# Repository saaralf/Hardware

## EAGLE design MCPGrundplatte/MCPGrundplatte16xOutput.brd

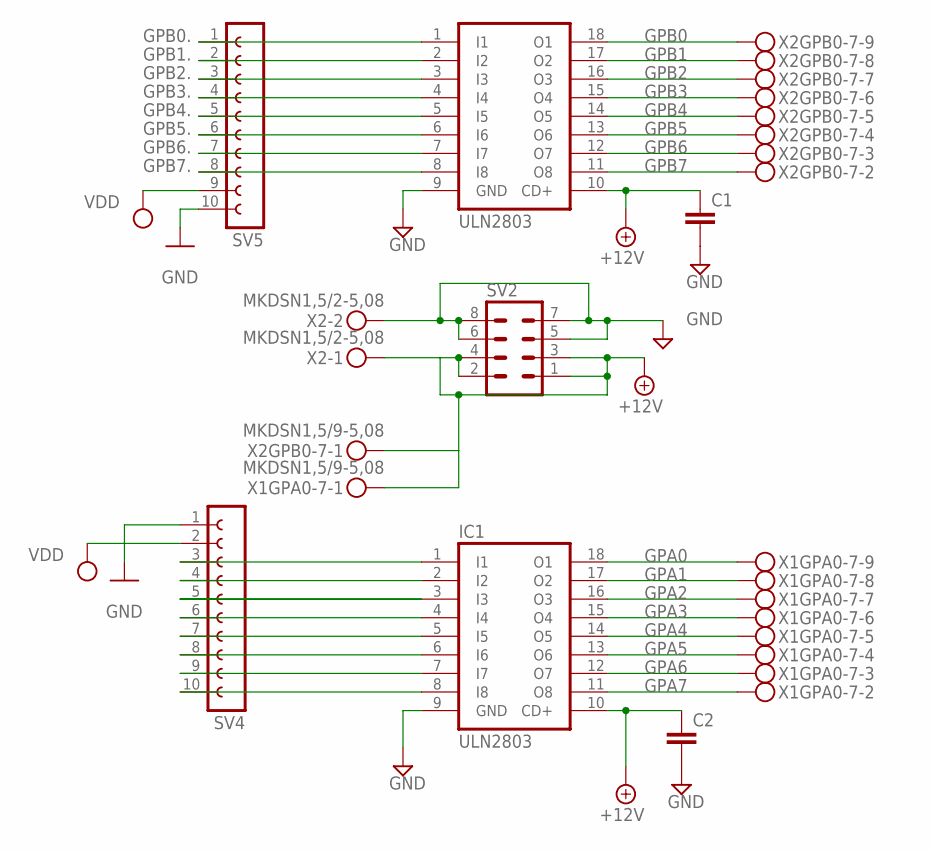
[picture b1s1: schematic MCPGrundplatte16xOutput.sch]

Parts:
C1, C2: C-EU025-024X044; C025-024X044
IC1, IC4: ULN2803; DIL18
SV2: MA04-2
SV4, SV5: FE10-1; FE10
X1GPA0-7, X2GPB0-7: MKDSN1,5/9-5,08
X2: MKDSN1,5/2-5,08

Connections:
+12V: C1.1, C2.1, IC1.10 (CD+), IC4.10 (CD+), SV2.1, SV2.2, SV2.3, SV2.4, X1GPA0-7.1, X2.1, X2GPB0-7.1
GND: C1.2, C2.2, IC1.9 (GND), IC4.9 (GND), SV2.5, SV2.6, SV2.7, SV2.8, SV4.1, SV5.10, X2.2
GPA0: IC1.18 (O1), X1GPA0-7.9
GPA1: IC1.17 (O2), X1GPA0-7.8
GPA2: IC1.16 (O3), X1GPA0-7.7
GPA3: IC1.15 (O4), X1GPA0-7.6
GPA4: IC1.14 (O5), X1GPA0-7.5
GPA5: IC1.13 (O6), X1GPA0-7.4
GPA6: IC1.12 (O7), X1GPA0-7.3
GPA7: IC1.11 (O8), X1GPA0-7.2
GPB0: IC4.18 (O1), X2GPB0-7.9
GPB0.: IC4.1 (I1), SV5.1
GPB1: IC4.17 (O2), X2GPB0-7.8
GPB1.: IC4.2 (I2), SV5.2
GPB2: IC4.16 (O3), X2GPB0-7.7
GPB2.: IC4.3 (I3), SV5.3
GPB3: IC4.15 (O4), X2GPB0-7.6
GPB3.: IC4.4 (I4), SV5.4
GPB4: IC4.14 (O5), X2GPB0-7.5
GPB4.: IC4.5 (I5), SV5.5
GPB5: IC4.13 (O6), X2GPB0-7.4
GPB5.: IC4.6 (I6), SV5.6
GPB6: IC4.12 (O7), X2GPB0-7.3
GPB6.: IC4.7 (I7), SV5.7
GPB7: IC4.11 (O8), X2GPB0-7.2
GPB7.: IC4.8 (I8), SV5.8
unnamed: IC1.6 (I6), SV4.8
unnamed: IC1.1 (I1), SV4.3
unnamed: IC1.2 (I2), SV4.4
unnamed: IC1.3 (I3), SV4.5
unnamed: IC1.4 (I4), SV4.6
unnamed: IC1.5 (I5), SV4.7
unnamed: IC1.7 (I7), SV4.9
unnamed: IC1.8 (I8), SV4.10
VDD: SV4.2, SV5.9

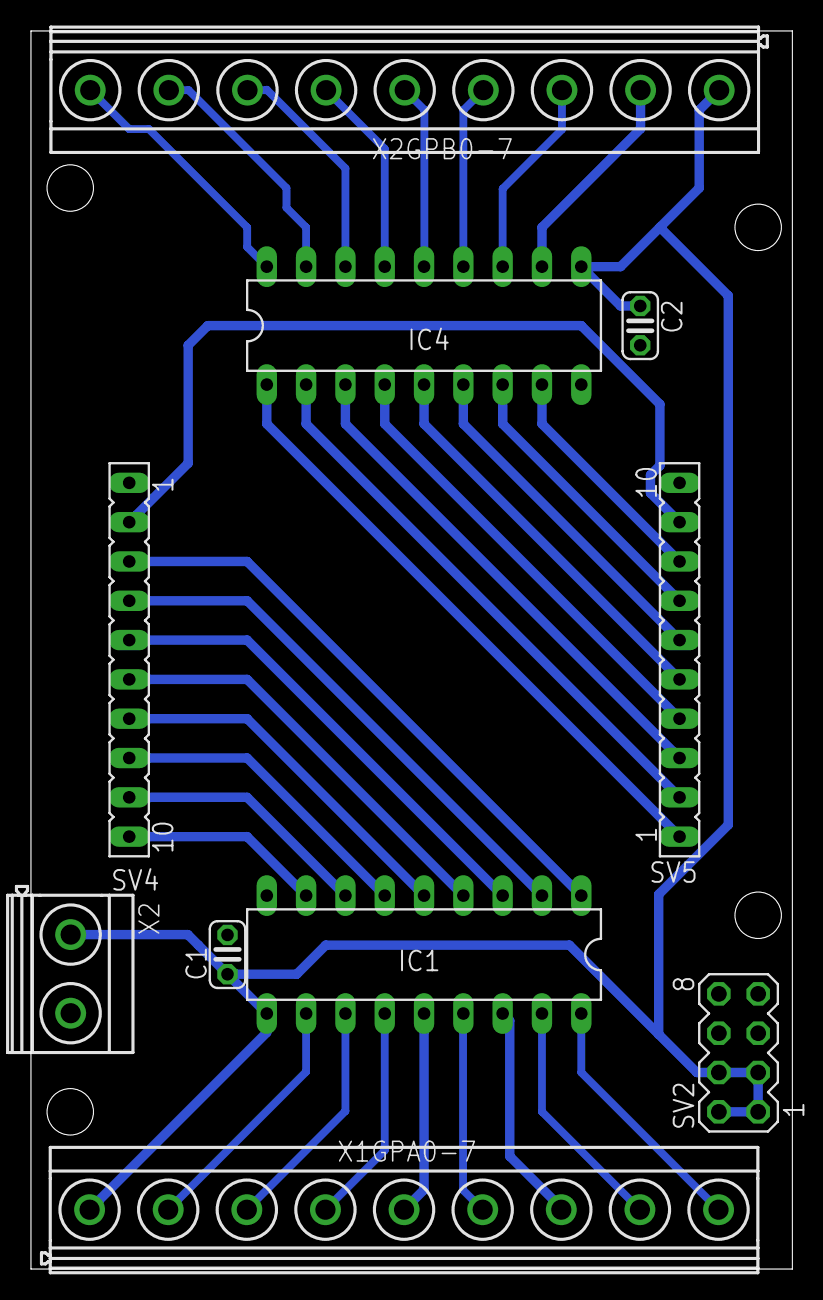
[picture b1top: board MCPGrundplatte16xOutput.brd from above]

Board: 2 copper layers, 49.2 x 80.0 mm, 10 parts (0 on the bottom side), 35 nets.

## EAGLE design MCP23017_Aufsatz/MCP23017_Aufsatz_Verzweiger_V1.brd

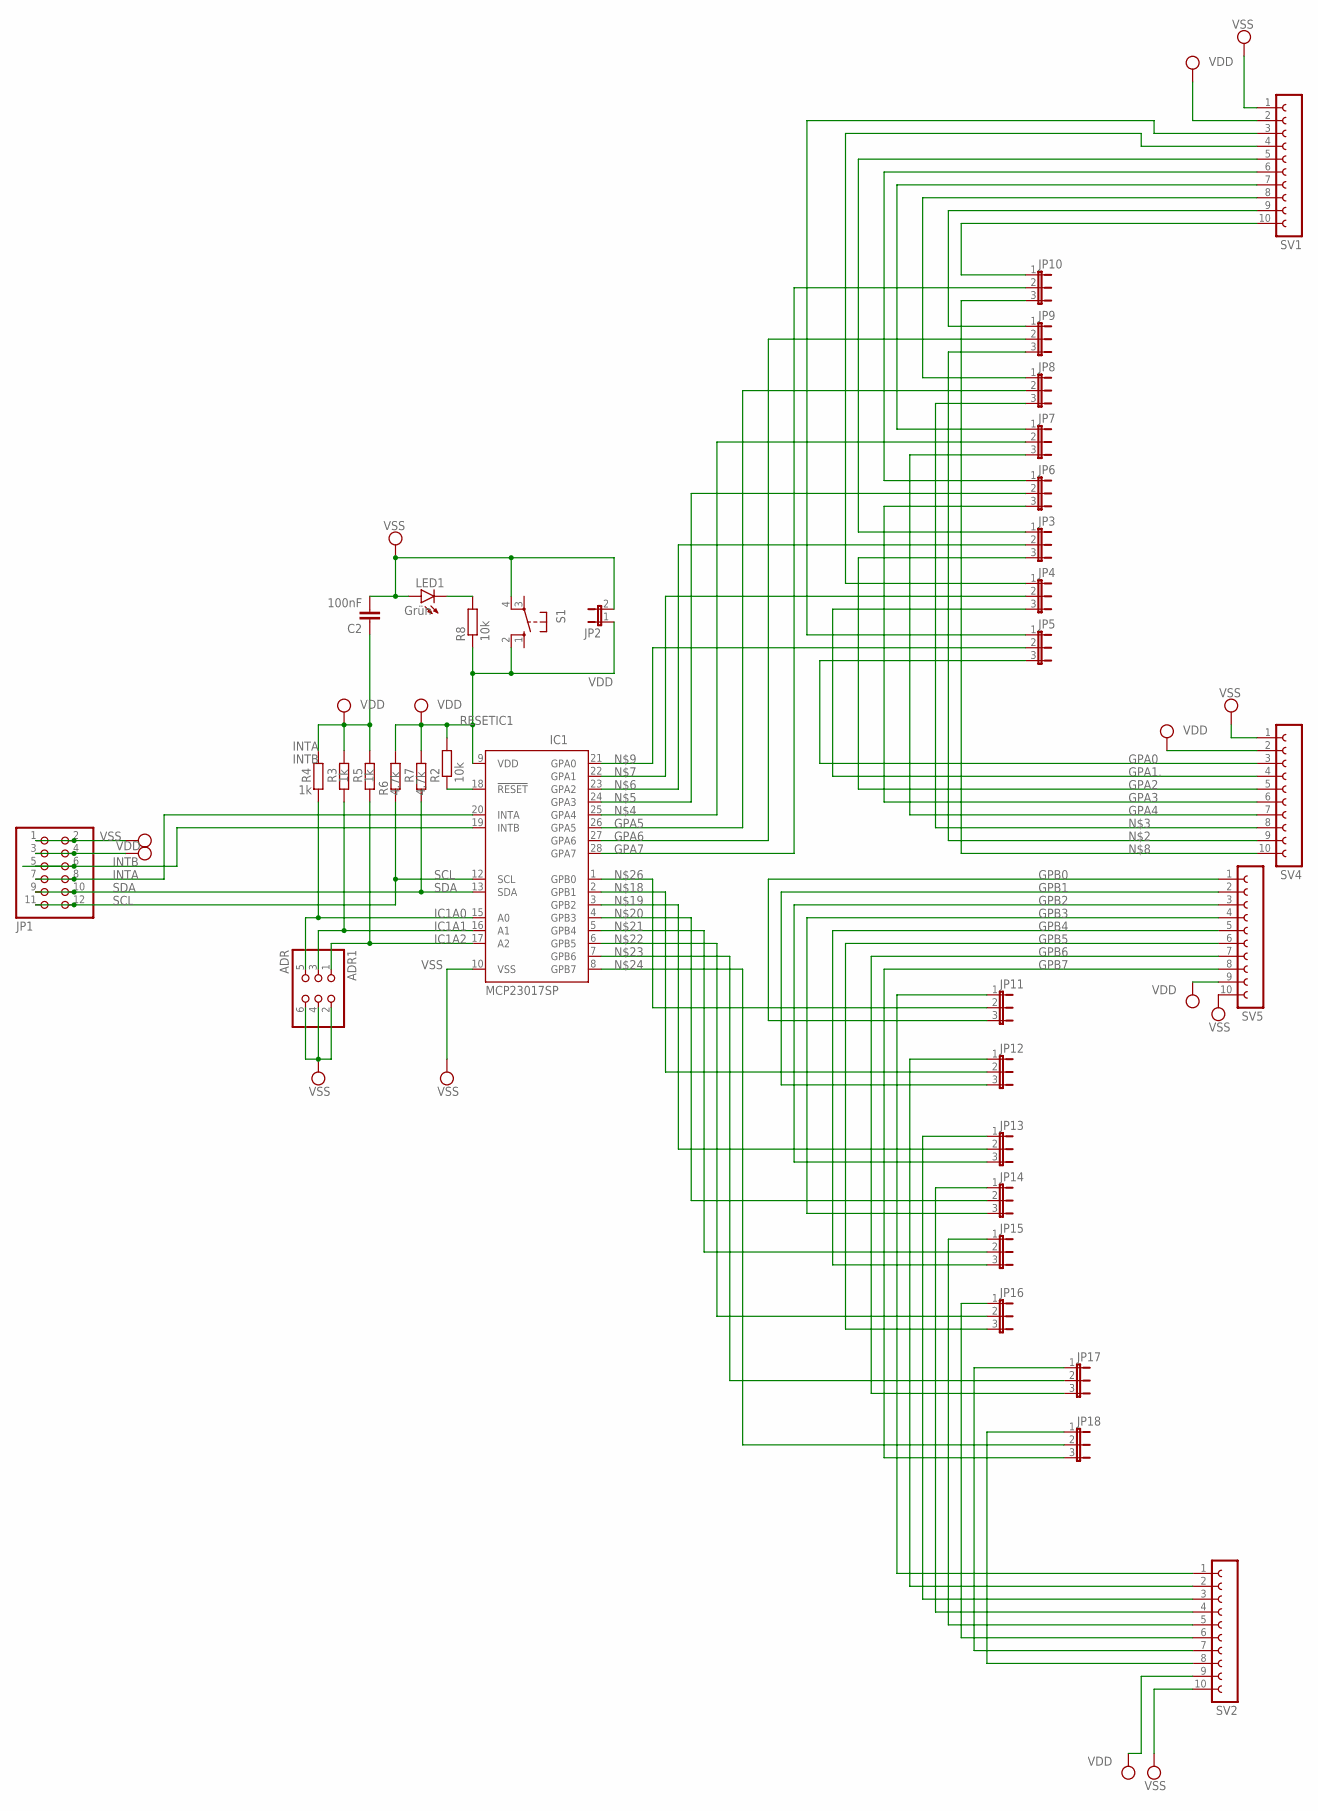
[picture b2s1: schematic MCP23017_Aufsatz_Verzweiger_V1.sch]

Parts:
ADR1: ADR; 2X03
C2: 100nF; C025-025X050
IC1: MCP23017SP; DIL28-3
JP1: JP1; 2X06/90
JP2: JP1E; JP1
JP3, JP4, JP5, JP6, JP7, JP8, JP9, JP10, JP11, JP12, JP13, JP14, JP15, JP16, JP17, JP18: JP2E; JP2
LED1: Grün; LED3MM
R2, R8: 10k; 0207/10
R3, R4, R5: 1k; 0207/10
R6, R7: 4,7k; 0207/10
S1: 10-XX; B3F-10XX
SV1, SV2, SV4, SV5: FE10-1; FE10

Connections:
GPA0: JP5.3, SV4.3
GPA1.: JP4.3, SV4.4
GPA2: JP3.3, SV4.5
GPA3: JP6.3, SV4.6
GPA4: JP7.3, SV4.7
GPA5: IC1.26 (GPA5), JP8.2
GPA6: IC1.27 (GPA6), JP9.2
GPA7: IC1.28 (GPA7), JP10.2
GPB0: JP11.3, SV5.1
GPB1: JP12.3, SV5.2
GPB2: JP13.3, SV5.3
GPB3: JP14.3, SV5.4
GPB4: JP15.3, SV5.5
GPB5: JP16.3, SV5.6
GPB6: JP17.3, SV5.7
GPB7: JP18.3, SV5.8
IC1A0: ADR1.5, IC1.15 (A0), R4.1
IC1A1: ADR1.3, IC1.16 (A1), R3.1
IC1A2: ADR1.1, IC1.17 (A2), R5.1
INTA: IC1.20 (INTA), JP1.7, JP1.8
INTB: IC1.19 (INTB), JP1.5, JP1.6
unnamed: LED1.K (C), R8.2
unnamed: JP9.3, SV4.9
unnamed: JP8.3, SV4.8
unnamed: IC1.25 (GPA4), JP7.2
unnamed: IC1.24 (GPA3), JP6.2
unnamed: IC1.23 (GPA2), JP3.2
unnamed: IC1.22 (GPA1), JP4.2
unnamed: JP10.3, SV4.10
unnamed: IC1.21 (GPA0), JP5.2
unnamed: JP10.1, SV1.10
unnamed: JP9.1, SV1.9
unnamed: JP8.1, SV1.8
unnamed: JP7.1, SV1.7
unnamed: JP6.1, SV1.6
unnamed: JP3.1, SV1.5
unnamed: JP4.1, SV1.4
unnamed: JP5.1, SV1.3
unnamed: IC1.2 (GPB1), JP12.2
unnamed: IC1.3 (GPB2), JP13.2
unnamed: IC1.4 (GPB3), JP14.2
unnamed: IC1.5 (GPB4), JP15.2
unnamed: IC1.6 (GPB5), JP16.2
unnamed: IC1.7 (GPB6), JP17.2
unnamed: IC1.8 (GPB7), JP18.2
unnamed: JP11.1, SV2.1
unnamed: IC1.1 (GPB0), JP11.2
unnamed: JP12.1, SV2.2
unnamed: JP13.1, SV2.3
unnamed: JP14.1, SV2.4
unnamed: JP15.1, SV2.5
unnamed: JP16.1, SV2.6
unnamed: JP17.1, SV2.7
unnamed: JP18.1, SV2.8
RESETIC1: IC1.18 (!RESET), R2.1
SCL: IC1.12 (SCL), JP1.11, JP1.12, R6.1
SDA: IC1.13 (SDA), JP1.9, JP1.10, R7.1
VDD: C2.1, IC1.9 (VDD), JP1.3, JP1.4, JP2.1, R2.2, R3.2, R4.2, R5.2, R6.2, R7.2, R8.1, S1.2 (S1), SV1.2, SV2.9, SV4.2, SV5.9
VSS: ADR1.2, ADR1.4, ADR1.6, C2.2, IC1.10 (VSS), JP1.1, JP1.2, JP2.2, LED1.A, S1.4 (P1), SV1.1, SV2.10, SV4.1, SV5.10

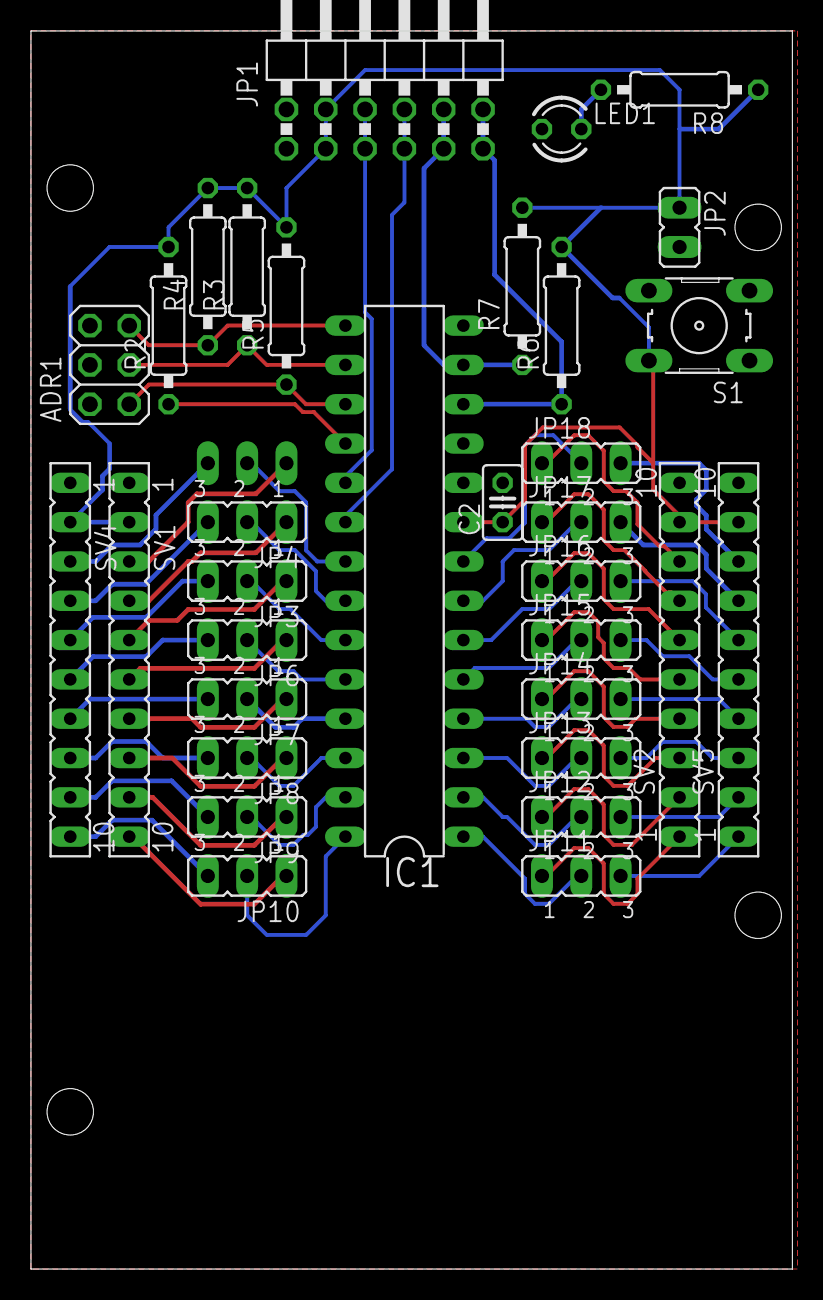
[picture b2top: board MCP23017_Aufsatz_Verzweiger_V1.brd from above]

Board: 2 copper layers, 49.2 x 80.0 mm, 34 parts (1 on the bottom side), 59 nets.

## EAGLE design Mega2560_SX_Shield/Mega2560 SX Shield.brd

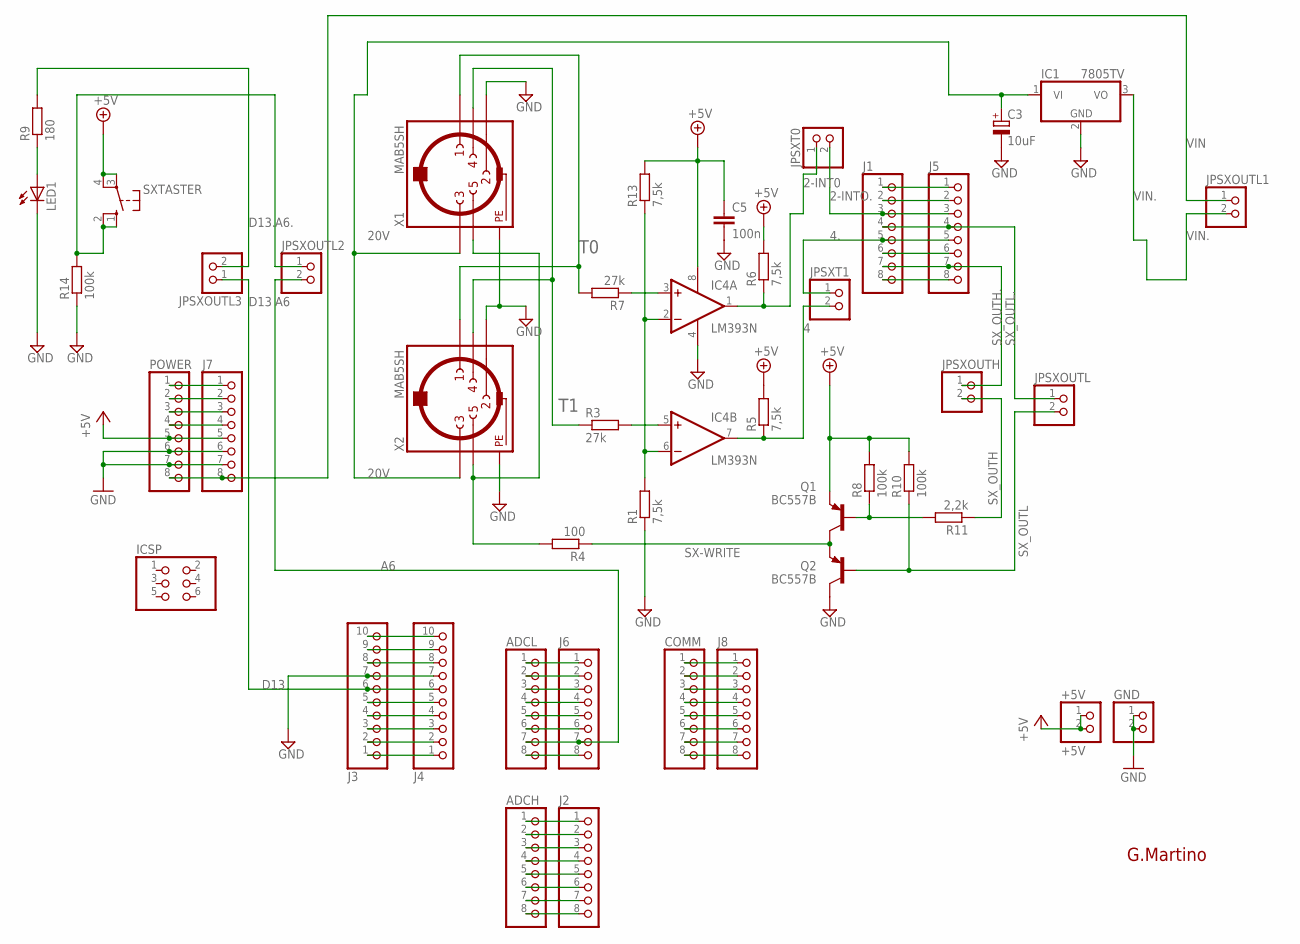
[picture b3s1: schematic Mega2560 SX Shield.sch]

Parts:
+5V: +5V; 1X02
ADCH: PINHD-1X8TH; 1X08-TH
ADCL: PINHD-1X8TH; 1X08-TH
C3: 10uF; TT2D5
C5: 100n; C050-025X075
COMM: PINHD-1X8TH; 1X08-TH
GND: PINHD-1X2; 1X02
IC1: 7805TV; TO220V
IC4: LM393N; DIL08
ICSP: PINHD-2X3; 2X03
J1, J2, J5, J6, J7, J8: PINHD-1X8TH; 1X08-TH
J3, J4: PINHD-1X10TH; 1X10-TH
JPSXOUTH: PINHD-1X2; 1X02
JPSXOUTL, JPSXOUTL1, JPSXOUTL2, JPSXOUTL3: PINHD-1X2; 1X02
JPSXT0, JPSXT1: PINHD-1X2; 1X02
LED1: LED3MM
POWER: PINHD-1X8TH; 1X08-TH
Q1, Q2: BC557B; TO92-EBC
R1, R5, R6, R13: 7,5k; 0207/10
R3, R7: 27k; 0207/10
R4: 100; 0207/10
R8, R10, R14: 100k; 0207/10
R9: 180; 0207/10
R11: 2,2k; 0207/10
SXTASTER: 10-XX; B3F-10XX
X1, X2: MAB5SH

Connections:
2-INT0: IC4.1 (OUT), JPSXT0.1, R6.1
2-INTO.: J1.3, J5.3, JPSXT0.2
4: IC4.7 (OUT), JPSXT1.2, R5.1
4.: J1.5, J5.5, JPSXT1.1
20V: C3.+, IC1.1 (VI), X1.3, X2.3
+5V: +5V.1, +5V.2, C5.1, IC4.8 (V+), J7.5, POWER.5, Q1.E, R5.2, R6.2, R8.2, R10.2, R13.2, SXTASTER.3, SXTASTER.4 (P1)
A6: ADCL.7, J6.7, JPSXOUTL2.2
A6.: JPSXOUTL2.1, R14.2, SXTASTER.1 (S), SXTASTER.2 (S1)
D13: J3.6, J4.6, JPSXOUTL3.1
D13.: JPSXOUTL3.2, R9.2
GND: C3.-, C5.2, GND.1, GND.2, IC1.2 (GND), IC4.4 (V-), J3.7, J4.7, J7.6, J7.7, LED1.K (C), POWER.6, POWER.7, Q2.C, R1.1, R14.1, X1.2, X1.PE, X1.PE@ (PE), X1.PE@1 (PE), X1.PE@2 (PE), X2.2, X2.PE, X2.PE@ (PE), X2.PE@1 (PE), X2.PE@2 (PE)
unnamed: IC4.3 (+IN), R7.1
unnamed: J3.1, J4.1
unnamed: J1.2, J5.2
unnamed: J3.4, J4.4
unnamed: J3.2, J4.2
unnamed: J3.3, J4.3
unnamed: J1.1, J5.1
unnamed: J1.6, J5.6
unnamed: J1.8, J5.8
unnamed: ADCL.1, J6.1
unnamed: ADCL.2, J6.2
unnamed: ADCL.3, J6.3
unnamed: ADCL.4, J6.4
unnamed: ADCL.5, J6.5
unnamed: ADCL.6, J6.6
unnamed: ADCL.8, J6.8
unnamed: ADCH.1, J2.1
unnamed: ADCH.2, J2.2
unnamed: ADCH.3, J2.3
unnamed: ADCH.4, J2.4
unnamed: ADCH.5, J2.5
unnamed: ADCH.6, J2.6
unnamed: J7.4, POWER.4
unnamed: J3.9, J4.9
unnamed: ADCH.7, J2.7
unnamed: ADCH.8, J2.8
unnamed: COMM.1, J8.1
unnamed: COMM.2, J8.2
unnamed: COMM.3, J8.3
unnamed: COMM.4, J8.4
unnamed: COMM.5, J8.5
unnamed: COMM.6, J8.6
unnamed: COMM.7, J8.7
unnamed: COMM.8, J8.8
unnamed: J3.5, J4.5
unnamed: J7.2, POWER.2
unnamed: J7.1, POWER.1
unnamed: J3.8, J4.8
unnamed: J3.10, J4.10
unnamed: IC4.5 (+IN), R3.2
unnamed: IC4.2 (-IN), IC4.6 (-IN), R1.2, R13.1
unnamed: R4.2, X1.5, X2.5
unnamed: LED1.A, R9.1
unnamed: Q1.B, R8.1, R11.2
RESET: J7.3, POWER.3
SX-WRITE: Q1.C, Q2.E, R4.1
SX_OUTH: JPSXOUTH.2, R11.1
SX_OUTH.: J1.7, J5.7, JPSXOUTH.1
SX_OUTL: JPSXOUTL.2, Q2.B, R10.1
SX_OUTL.: J1.4, J5.4, JPSXOUTL.1
T0: R7.2, X1.1, X2.1
T1: R3.1, X1.4, X2.4
VIN: J7.8, JPSXOUTL1.1, POWER.8
VIN.: IC1.3 (VO), JPSXOUTL1.2

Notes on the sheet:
G.Martino

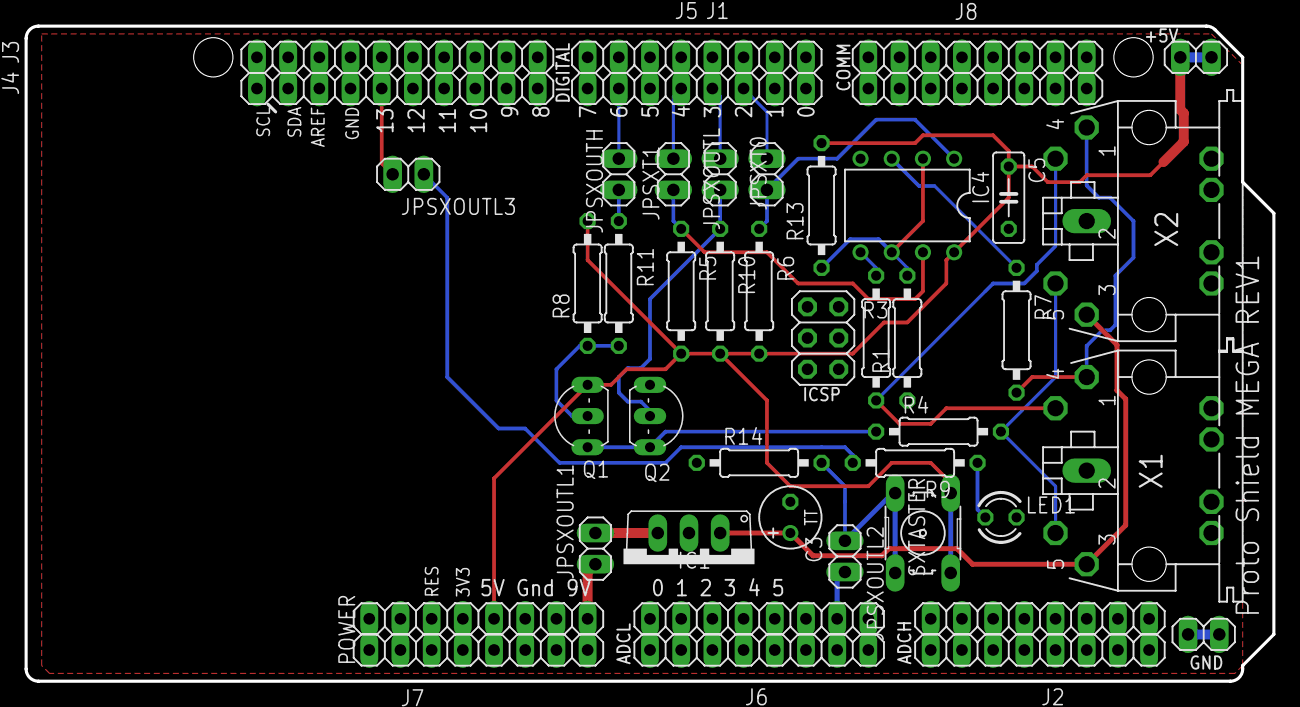
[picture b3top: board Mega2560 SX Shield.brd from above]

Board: 2 copper layers, 101.6 x 53.3 mm, 44 parts (0 on the bottom side), 65 nets.

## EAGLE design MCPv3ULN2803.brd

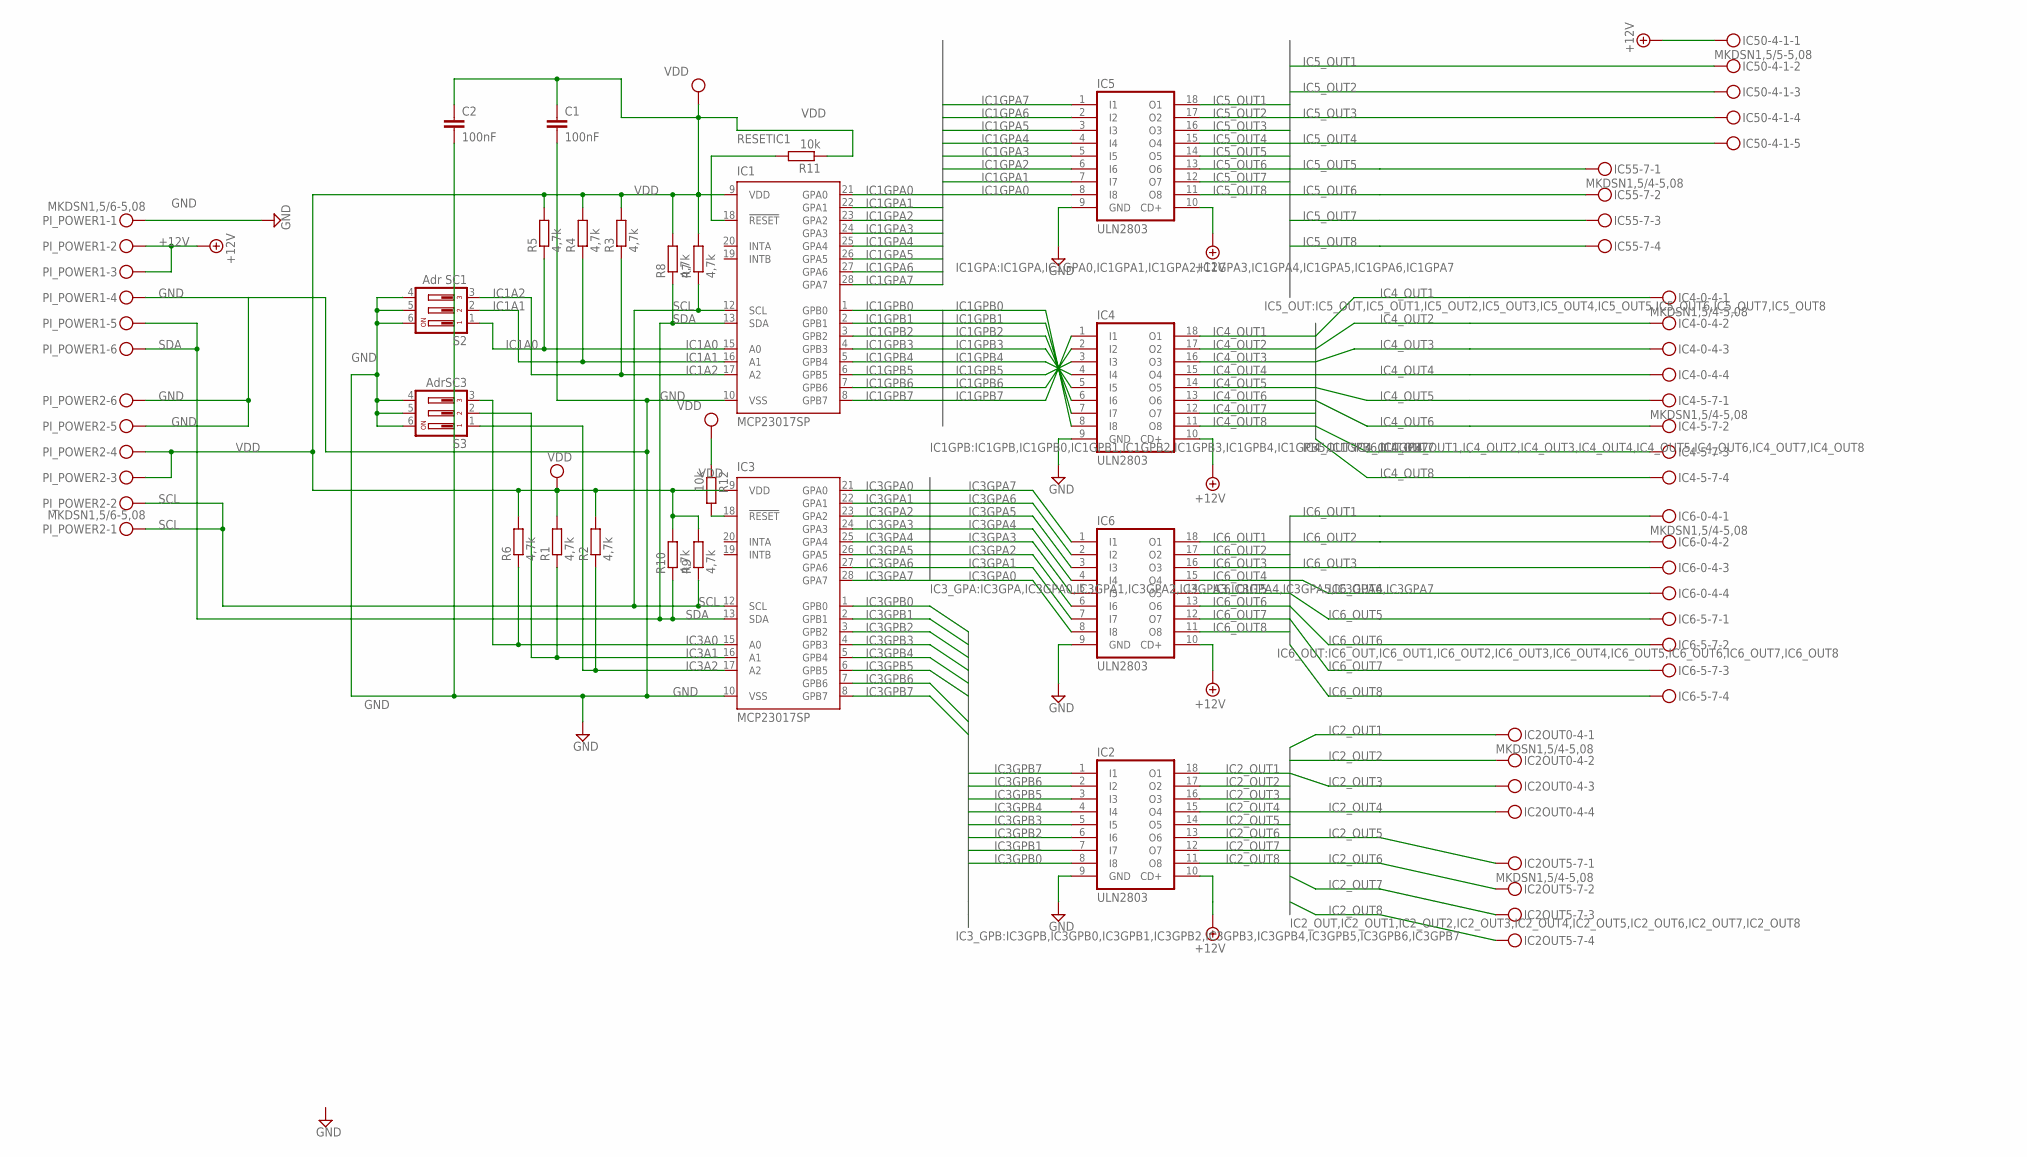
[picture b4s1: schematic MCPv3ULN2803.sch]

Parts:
C1, C2: 100nF; C025_050-025X075
IC1, IC3: MCP23017SP; DIL28-3
IC2, IC4, IC5, IC6: ULN2803; DIL18
IC2OUT0-4, IC2OUT5-7, IC4-0-4, IC4-5-7, IC6-0-4, IC6-5-7, IC55-7: MKDSN1,5/4-5,08
IC50-4-1: MKDSN1,5/5-5,08
PI_POWER1, PI_POWER2: MKDSN1,5/6-5,08
R1, R2, R3, R4, R5, R6, R7, R8, R9, R10: 4,7k; 0204/7
R11, R12: 10k; 0204/7
S2: Adr SC1; DIP03YL
S3: AdrSC3; DIP03YL

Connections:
+12V: IC2.10 (CD+), IC4.10 (CD+), IC5.10 (CD+), IC6.10 (CD+), IC50-4-1.1, PI_POWER1.2, PI_POWER1.3
GND: C1.2, C2.2, IC1.10 (VSS), IC2.9 (GND), IC3.10 (VSS), IC4.9 (GND), IC5.9 (GND), IC6.9 (GND), PI_POWER1.1, PI_POWER1.4, PI_POWER2.5, PI_POWER2.6, S2.4, S2.5, S2.6, S3.4, S3.5, S3.6
IC1A0: IC1.15 (A0), R5.1, S2.1
IC1A1: IC1.16 (A1), R4.1, S2.2
IC1A2: IC1.17 (A2), R3.1, S2.3
IC1GPA0: IC1.21 (GPA0), IC5.8 (I8)
IC1GPA1: IC1.22 (GPA1), IC5.7 (I7)
IC1GPA2: IC1.23 (GPA2), IC5.6 (I6)
IC1GPA3: IC1.24 (GPA3), IC5.5 (I5)
IC1GPA4: IC1.25 (GPA4), IC5.4 (I4)
IC1GPA5: IC1.26 (GPA5), IC5.3 (I3)
IC1GPA6: IC1.27 (GPA6), IC5.2 (I2)
IC1GPA7: IC1.28 (GPA7), IC5.1 (I1)
IC1GPB0: IC1.1 (GPB0), IC4.8 (I8)
IC1GPB1: IC1.2 (GPB1), IC4.7 (I7)
IC1GPB2: IC1.3 (GPB2), IC4.6 (I6)
IC1GPB3: IC1.4 (GPB3), IC4.5 (I5)
IC1GPB4: IC1.5 (GPB4), IC4.4 (I4)
IC1GPB5: IC1.6 (GPB5), IC4.3 (I3)
IC1GPB6: IC1.7 (GPB6), IC4.2 (I2)
IC1GPB7: IC1.8 (GPB7), IC4.1 (I1)
IC2_OUT1: IC2.18 (O1), IC2OUT0-4.1
IC2_OUT2: IC2.17 (O2), IC2OUT0-4.2
IC2_OUT3: IC2.16 (O3), IC2OUT0-4.3
IC2_OUT4: IC2.15 (O4), IC2OUT0-4.4
IC2_OUT5: IC2.14 (O5), IC2OUT5-7.1
IC2_OUT6: IC2.13 (O6), IC2OUT5-7.2
IC2_OUT7: IC2.12 (O7), IC2OUT5-7.3
IC2_OUT8: IC2.11 (O8), IC2OUT5-7.4
IC3A0: IC3.15 (A0), R6.1, S3.3
IC3A1: IC3.16 (A1), R1.1, S3.2
IC3A2: IC3.17 (A2), R2.1, S3.1
IC3GPA0: IC3.21 (GPA0), IC6.8 (I8)
IC3GPA1: IC3.22 (GPA1), IC6.7 (I7)
IC3GPA2: IC3.23 (GPA2), IC6.6 (I6)
IC3GPA3: IC3.24 (GPA3), IC6.5 (I5)
IC3GPA4: IC3.25 (GPA4), IC6.4 (I4)
IC3GPA5: IC3.26 (GPA5), IC6.3 (I3)
IC3GPA6: IC3.27 (GPA6), IC6.2 (I2)
IC3GPA7: IC3.28 (GPA7), IC6.1 (I1)
IC3GPB0: IC2.8 (I8), IC3.1 (GPB0)
IC3GPB1: IC2.7 (I7), IC3.2 (GPB1)
IC3GPB2: IC2.6 (I6), IC3.3 (GPB2)
IC3GPB3: IC2.5 (I5), IC3.4 (GPB3)
IC3GPB4: IC2.4 (I4), IC3.5 (GPB4)
IC3GPB5: IC2.3 (I3), IC3.6 (GPB5)
IC3GPB6: IC2.2 (I2), IC3.7 (GPB6)
IC3GPB7: IC2.1 (I1), IC3.8 (GPB7)
IC4_OUT1: IC4.18 (O1), IC4-0-4.1
IC4_OUT2: IC4.17 (O2), IC4-0-4.2
IC4_OUT3: IC4.16 (O3), IC4-0-4.3
IC4_OUT4: IC4.15 (O4), IC4-0-4.4
IC4_OUT5: IC4.14 (O5), IC4-5-7.1
IC4_OUT6: IC4.13 (O6), IC4-5-7.2
IC4_OUT7: IC4.12 (O7), IC4-5-7.3
IC4_OUT8: IC4.11 (O8), IC4-5-7.4
IC5_OUT1: IC5.18 (O1), IC50-4-1.2
IC5_OUT2: IC5.17 (O2), IC50-4-1.3
IC5_OUT3: IC5.16 (O3), IC50-4-1.4
IC5_OUT4: IC5.15 (O4), IC50-4-1.5
IC5_OUT5: IC5.14 (O5), IC55-7.1
IC5_OUT6: IC5.13 (O6), IC55-7.2
IC5_OUT7: IC5.12 (O7), IC55-7.3
IC5_OUT8: IC5.11 (O8), IC55-7.4
IC6_OUT1: IC6.18 (O1), IC6-0-4.1
IC6_OUT2: IC6.17 (O2), IC6-0-4.2
IC6_OUT3: IC6.16 (O3), IC6-0-4.3
IC6_OUT4: IC6.15 (O4), IC6-0-4.4
IC6_OUT5: IC6.14 (O5), IC6-5-7.1
IC6_OUT6: IC6.13 (O6), IC6-5-7.2
IC6_OUT7: IC6.12 (O7), IC6-5-7.3
IC6_OUT8: IC6.11 (O8), IC6-5-7.4
RESETIC1: IC1.18 (!RESET), R11.2
RESETIC3: IC3.18 (!RESET), R12.2
SCL: IC1.12 (SCL), IC3.12 (SCL), PI_POWER2.1, PI_POWER2.2, R7.1, R9.1
SDA: IC1.13 (SDA), IC3.13 (SDA), PI_POWER1.5, PI_POWER1.6, R8.1, R10.1
VDD: C1.1, C2.1, IC1.9 (VDD), IC3.9 (VDD), PI_POWER2.3, PI_POWER2.4, R1.2, R2.2, R3.2, R4.2, R5.2, R6.2, R7.2, R8.2, R9.2, R10.2, R11.1, R12.1

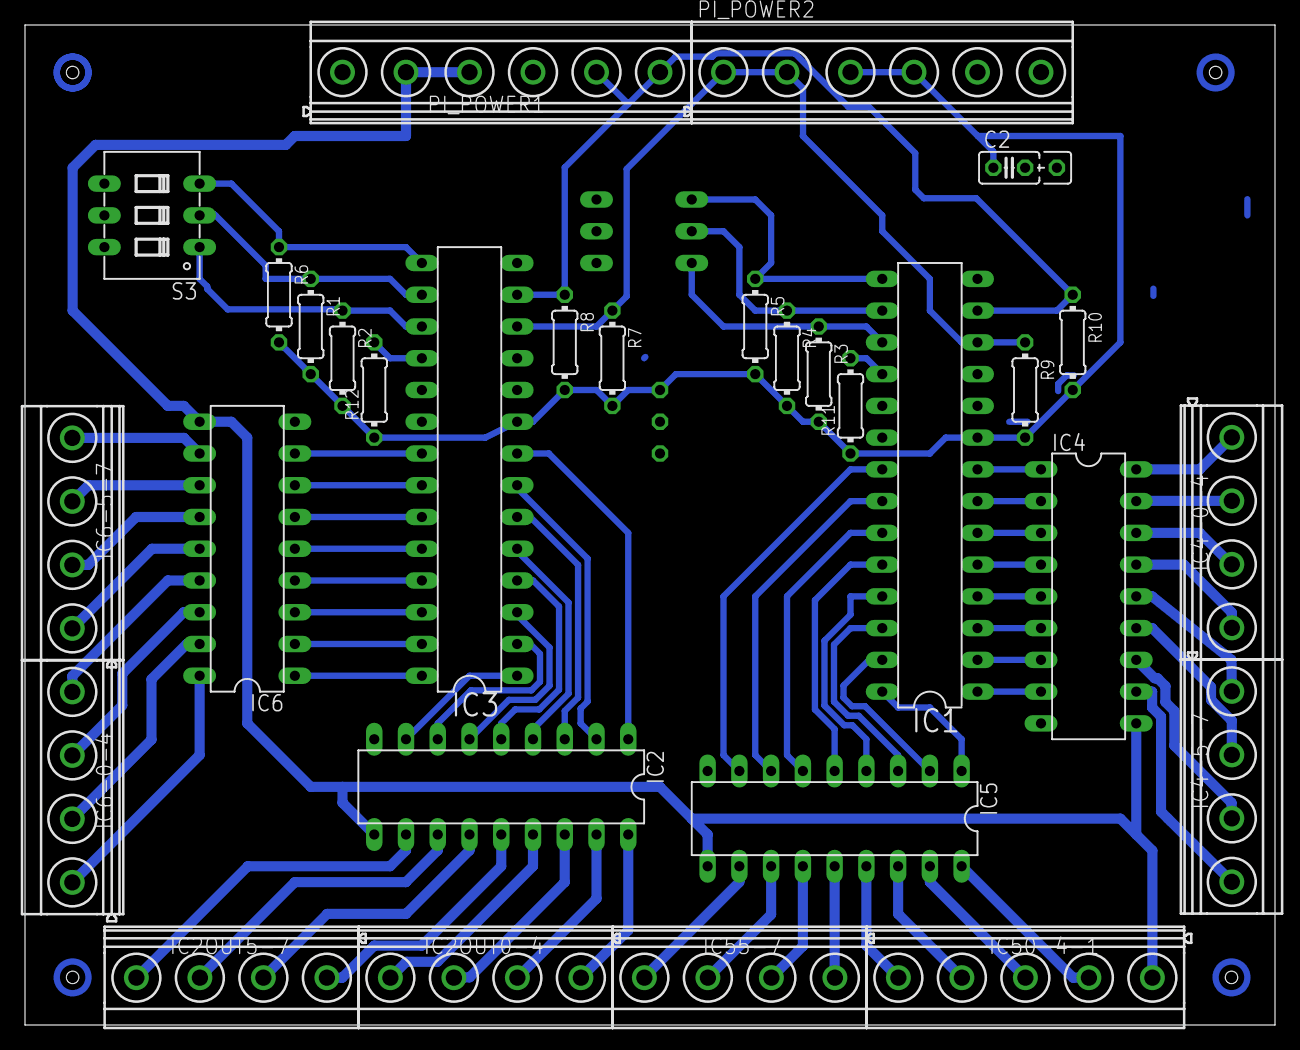
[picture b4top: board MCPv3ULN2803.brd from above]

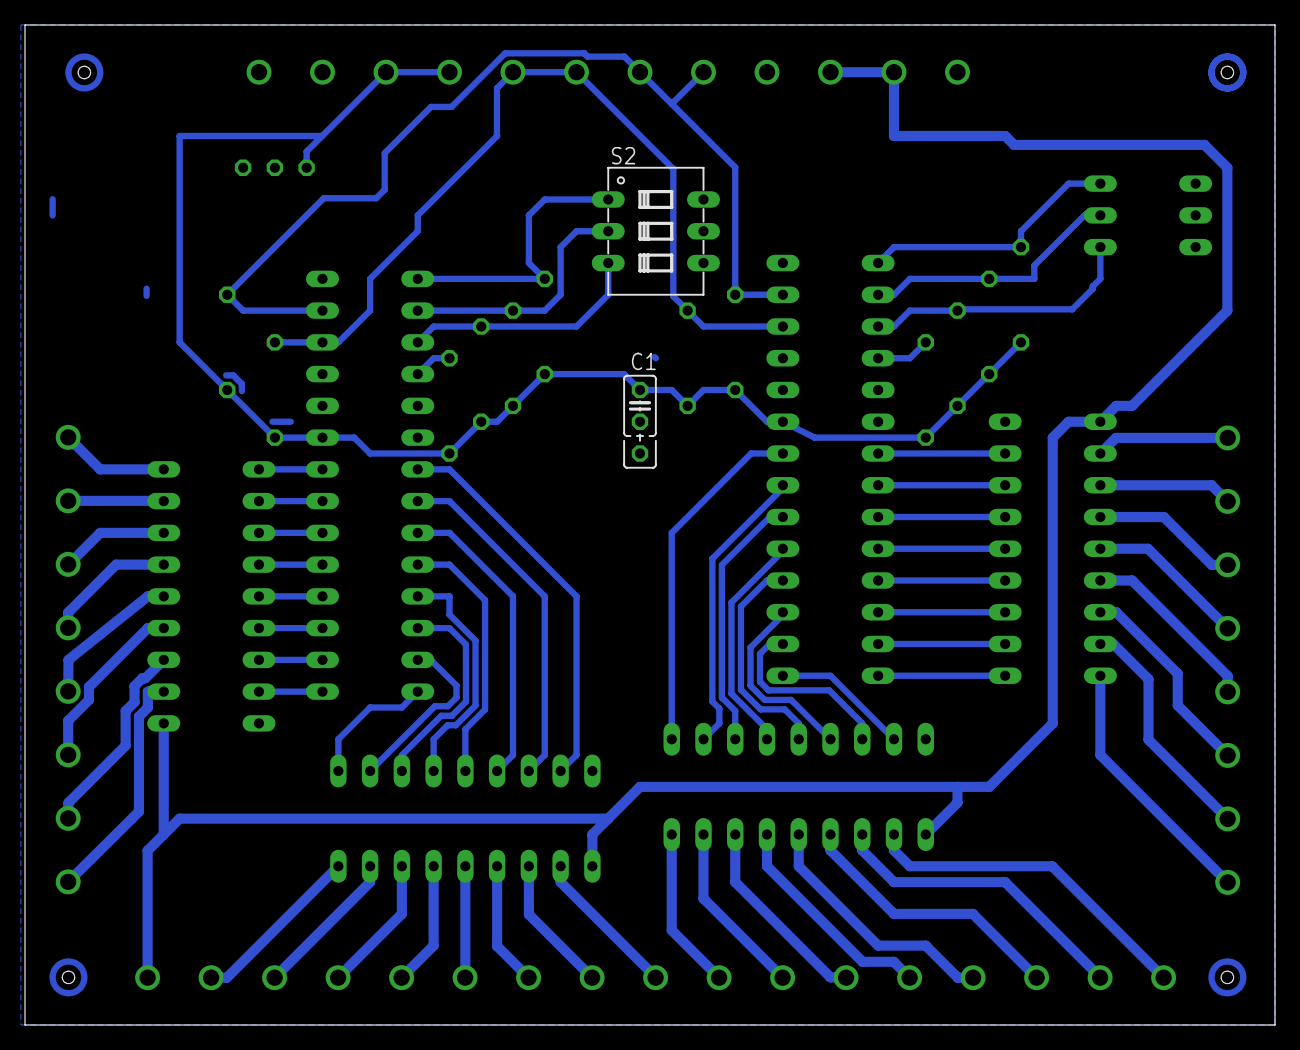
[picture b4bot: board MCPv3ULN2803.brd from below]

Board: 2 copper layers, 100.0 x 80.0 mm, 33 parts (2 on the bottom side), 77 nets.

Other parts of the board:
DRILEGEND: DRILEGEND

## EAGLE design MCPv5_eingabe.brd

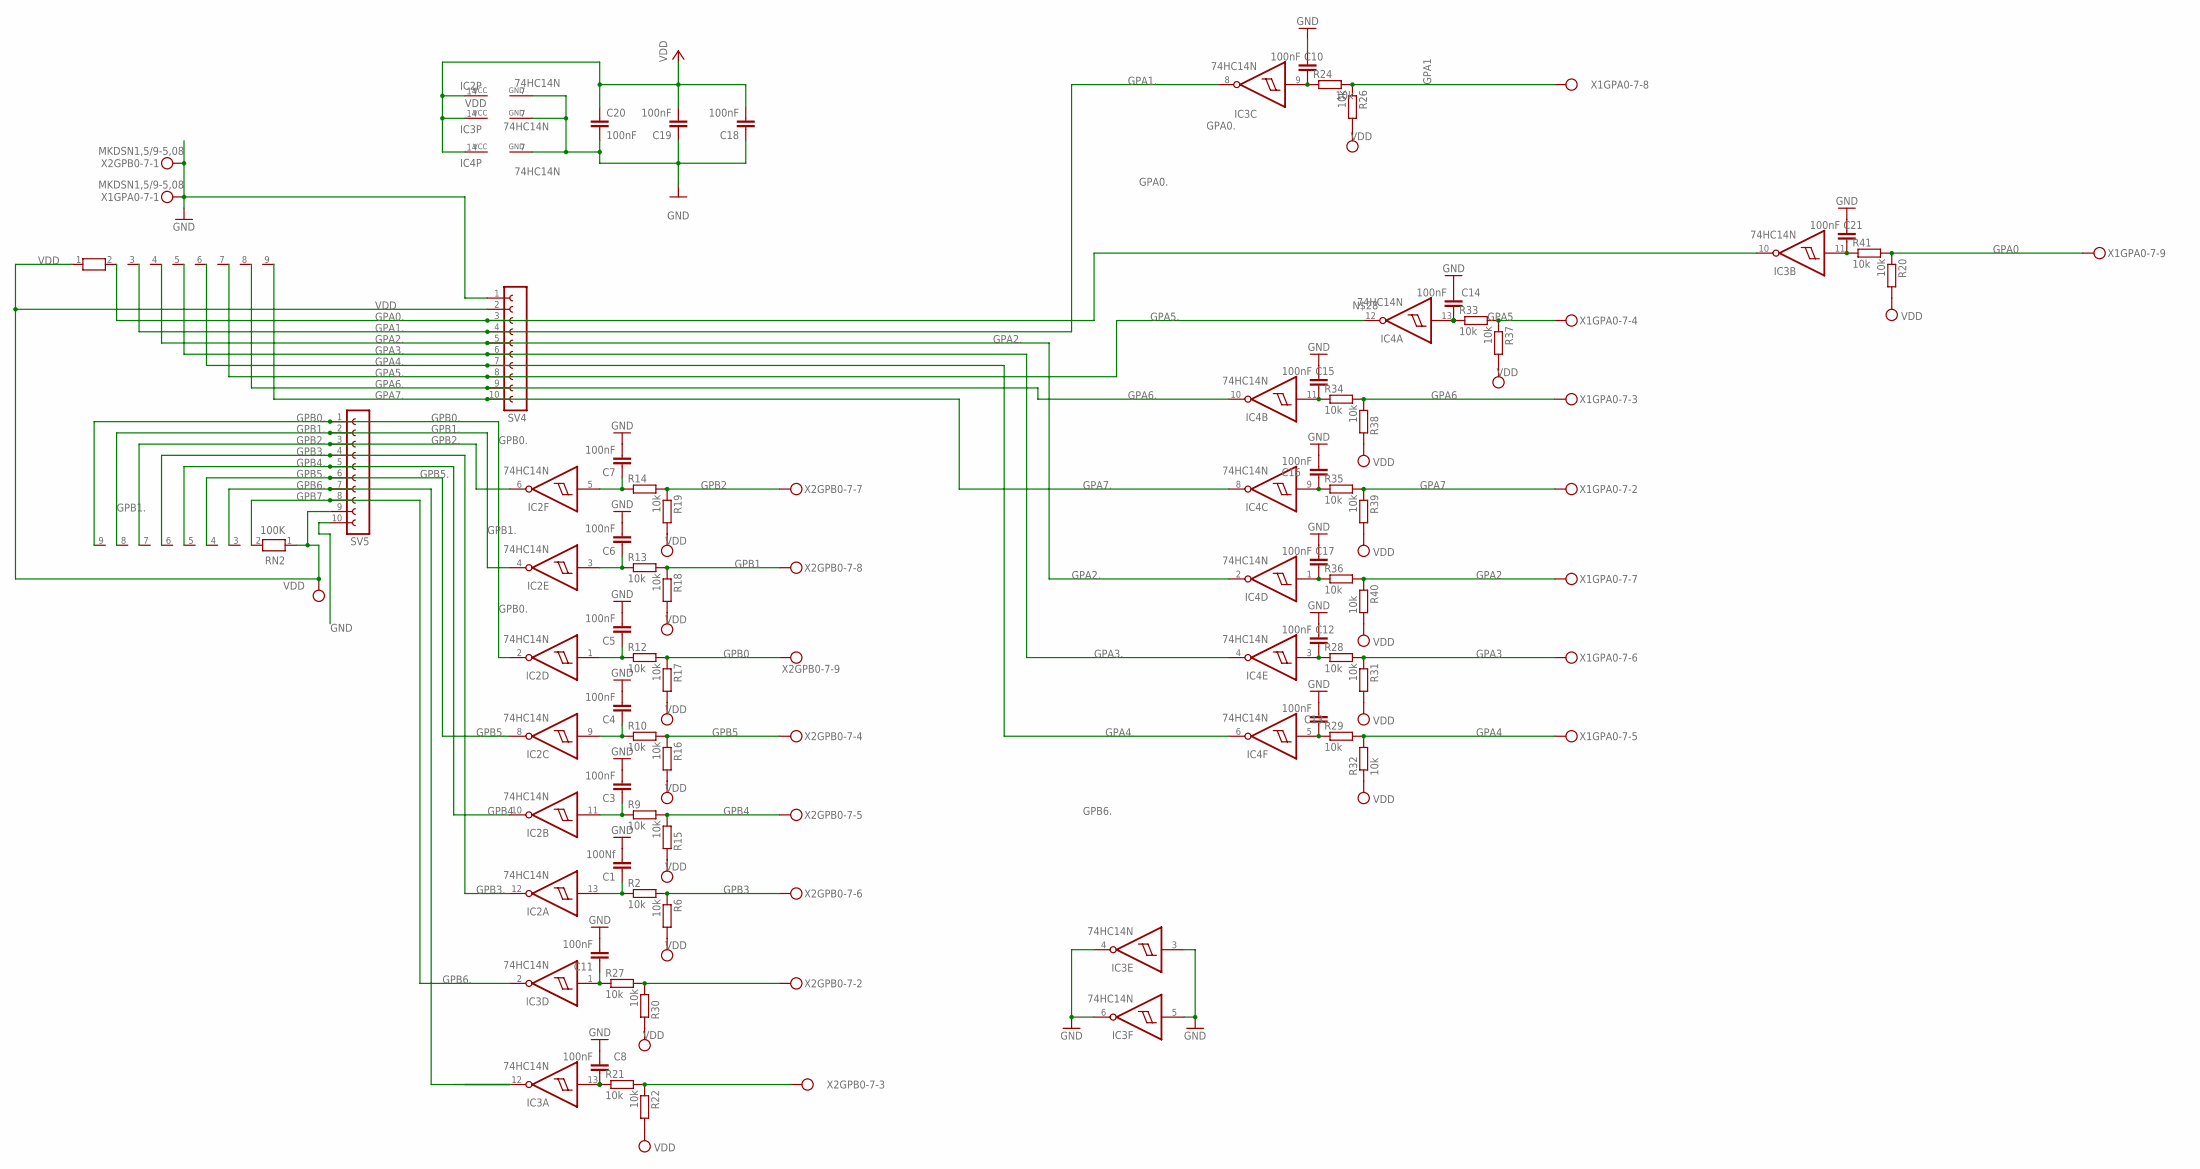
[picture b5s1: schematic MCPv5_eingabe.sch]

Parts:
C1: 100Nf; C025-024X044
C3, C4, C5, C6, C7, C8, C10, C11, C12, C13, C14, C15, C16, C17, C18, C19, C20, C21: 100nF; C025-024X044
IC2, IC3, IC4: 74HC14N; DIL14
R2, R6, R9, R10, R12, R13, R14, R15, R16, R17, R18, R19, R20, R21, R22, R24, R26, R27, R28, R29, R30, R31, R32, R33, R34, R35, R36, R37, R38, R39, R40, R41: 10k; 0204/7
RN1, RN2: 100K; RN-9
SV4, SV5: FE10-1; FE10
X1GPA0-7, X2GPB0-7: MKDSN1,5/9-5,08

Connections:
GND: C1.2, C3.2, C4.2, C5.2, C6.2, C7.2, C8.2, C10.2, C11.2, C12.2, C13.2, C14.2, C15.2, C16.2, C17.2, C18.1, C19.1, C20.2, C21.2, IC2.7 (GND), IC3.3 (I), IC3.4 (O), IC3.5 (I), IC3.6 (O), IC3.7 (GND), IC4.7 (GND), SV4.1, SV5.10, X1GPA0-7.1, X2GPB0-7.1
GPA0: R20.1, R41.2, X1GPA0-7.9
GPA0.: IC3.10 (O), RN1.2, SV4.3
GPA1: R24.2, R26.1, X1GPA0-7.8
GPA1.: IC3.8 (O), RN1.3, SV4.4
GPA2: R36.2, R40.1, X1GPA0-7.7
GPA2.: IC4.2 (O), RN1.4, SV4.5
GPA3: R28.2, R31.1, X1GPA0-7.6
GPA3.: IC4.4 (O), RN1.5, SV4.6
GPA4: R29.2, R32.2, X1GPA0-7.5
GPA4.: IC4.6 (O), RN1.6, SV4.7
GPA5: R33.2, R37.1, X1GPA0-7.4
GPA5.: IC4.12 (O), RN1.7, SV4.8
GPA6: R34.2, R38.1, X1GPA0-7.3
GPA6.: IC4.10 (O), RN1.8, SV4.9
GPA7: R35.2, R39.1, X1GPA0-7.2
GPA7.: IC4.8 (O), RN1.9, SV4.10
GPB0: R12.2, R17.1, X2GPB0-7.9
GPB0.: IC2.2 (O), RN2.9, SV5.1
GPB1: R13.2, R18.1, X2GPB0-7.8
GPB1.: IC2.4 (O), RN2.8, SV5.2
GPB2: R14.2, R19.1, X2GPB0-7.7
GPB2.: IC2.6 (O), RN2.7, SV5.3
GPB3: R2.2, R6.1, X2GPB0-7.6
GPB3.: IC2.12 (O), RN2.6, SV5.4
GPB4: R9.2, R15.1, X2GPB0-7.5
GPB4.: IC2.10 (O), RN2.5, SV5.5
GPB5: R10.2, R16.1, X2GPB0-7.4
GPB5.: IC2.8 (O), RN2.4, SV5.6
GPB6: R21.2, R22.1, X2GPB0-7.3
GPB6.: IC3.12 (O), RN2.3, SV5.7
GPB7: R27.2, R30.1, X2GPB0-7.2
GPB7.: IC3.2 (O), RN2.2, SV5.8
unnamed: C7.1, IC2.5 (I), R14.1
unnamed: C1.1, IC2.13 (I), R2.1
unnamed: C6.1, IC2.3 (I), R13.1
unnamed: C5.1, IC2.1 (I), R12.1
unnamed: C4.1, IC2.9 (I), R10.1
unnamed: C3.1, IC2.11 (I), R9.1
unnamed: C8.1, IC3.13 (I), R21.1
unnamed: C10.1, IC3.9 (I), R24.1
unnamed: C11.1, IC3.1 (I), R27.1
unnamed: C12.1, IC4.3 (I), R28.1
unnamed: C13.1, IC4.5 (I), R29.1
unnamed: C15.1, IC4.11 (I), R34.1
unnamed: C16.1, IC4.9 (I), R35.1
unnamed: C17.1, IC4.1 (I), R36.1
unnamed: C14.1, IC4.13 (I), R33.1
unnamed: C21.1, IC3.11 (I), R41.1
VDD: C18.2, C19.2, C20.1, IC2.14 (VCC), IC3.14 (VCC), IC4.14 (VCC), R6.2, R15.2, R16.2, R17.2, R18.2, R19.2, R20.2, R22.2, R26.2, R30.2, R31.2, R32.1, R37.2, R38.2, R39.2, R40.2, RN1.1, RN2.1, SV4.2, SV5.9

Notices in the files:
MCPv3ULN2803.brd:
Copyright 2019
